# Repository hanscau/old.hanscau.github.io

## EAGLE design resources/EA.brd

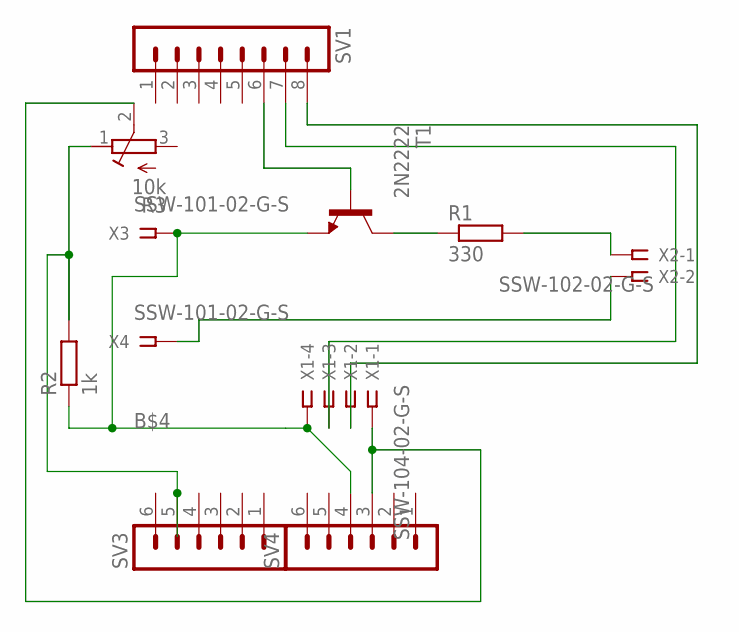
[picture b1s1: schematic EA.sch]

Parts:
R1: 330; 0207/10
R2: 1k; 0207/10
R3: 10k; RTRIMT93YA
SV1: MA08-1
SV3, SV4: MA06-1
T1: 2N2222; TO18
X1: SSW-104-02-G-S
X2: SSW-102-02-G-S
X3, X4: SSW-101-02-G-S

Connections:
B$4: R2.1, SV4.4, T1.1 (E), X1.4, X3.1
unnamed: R1.1, T1.3 (C)
unnamed: R1.2, X2.1
unnamed: SV1.6, T1.2 (B)
unnamed: R3.2 (S), SV4.3, X1.1
unnamed: SV1.7, X1.3
unnamed: SV1.8, X1.2
unnamed: X2.2, X4.1
unnamed: R2.2, R3.1 (E), SV3.5

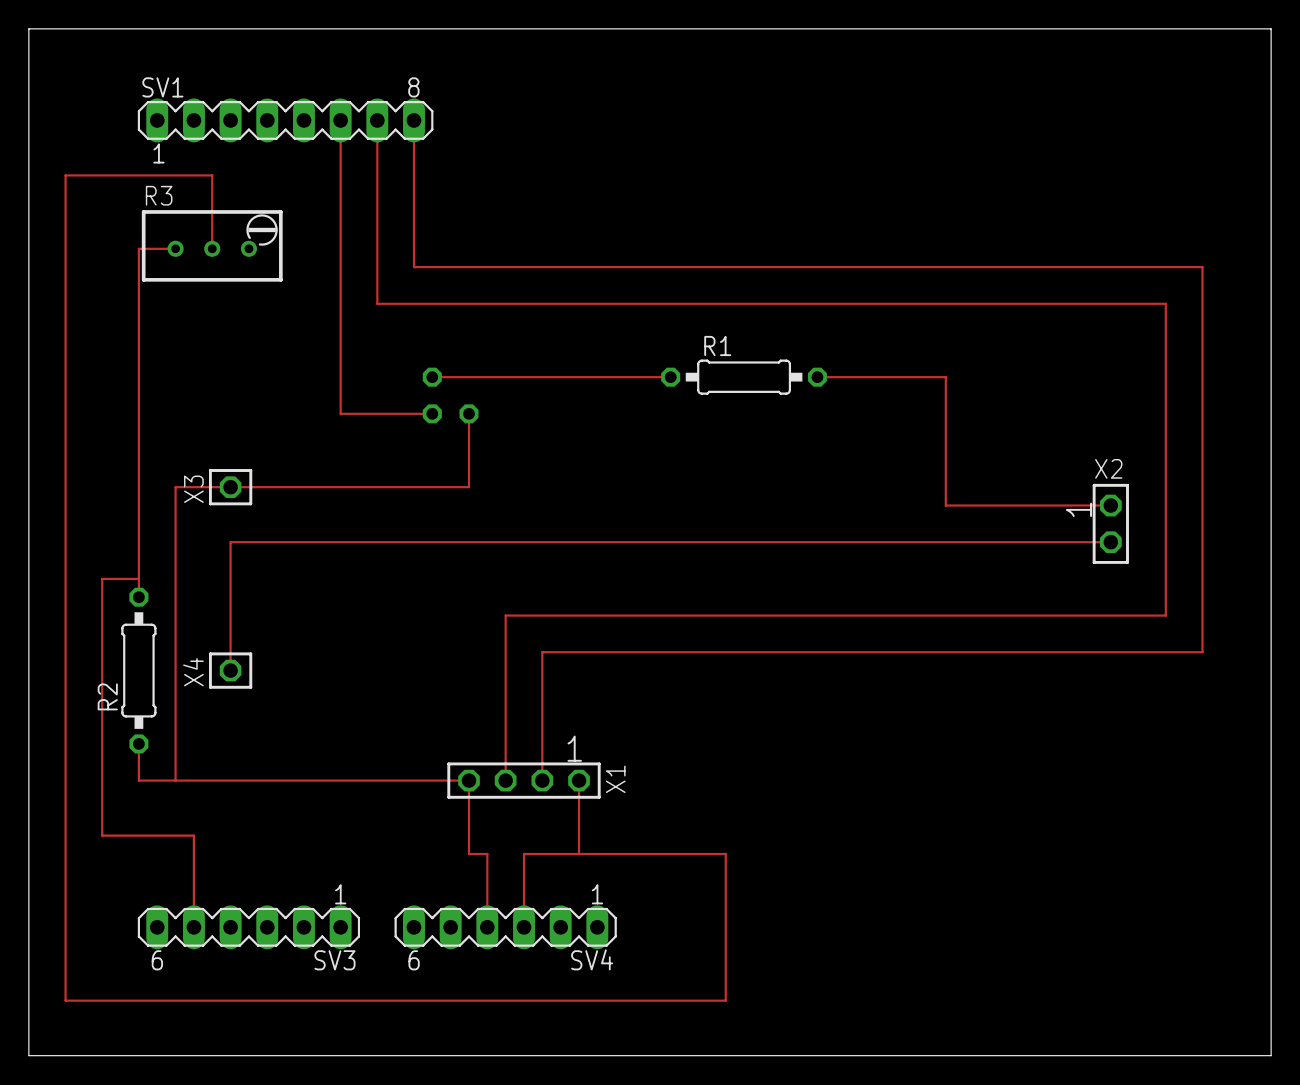
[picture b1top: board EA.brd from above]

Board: 2 copper layers, 86.0 x 71.1 mm, 11 parts (1 on the bottom side), 9 nets.

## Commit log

2018-09-25 Edit 1
    -Changed header and footer title
    -Added compile Darknet with CUDA and OpenCV
2018-09-26 Update 2
    -Finished OpenCV installation
    -Finished Ubuntu installation
    -changed title
    -changed css main padding
    -TODO: PICTURES
2018-09-26 SSH + Rpi
    -finished SSH + Rpi
    -added autoEdit auto navigation adder
2018-09-26 Revert "Update 2"
    This reverts commit 319ca2e53e9c3f57c753c12232fc271b25eb8960.
2018-09-26 Error stuff
2018-09-26 Fixed error
    zzzzz
2018-09-26 CSS edit
    part of fixing the error
2018-10-02 Rpi + SSH update
    Added Headless connection
2018-10-05 RPi complete headless guide
2018-10-05 Rpi Setup Minor Edit
    Added Pics
    Some mispelled stuff...
2018-10-08 ReVIsIon oN StuFf
    Changes to Object Detection
    Changes to RPi setup
2018-10-25 Added Portable PPB Detection
    -documentation for ball detection
    - added hopes and dreams
2019-06-29 Invisible Tripwire Alarm
    Created the page
    Added Content
    Added Resources
    Added Images
2019-06-30 Editted Inivisible Tripwire Alarm
    Changed schematic pic
    Changed youtube link
